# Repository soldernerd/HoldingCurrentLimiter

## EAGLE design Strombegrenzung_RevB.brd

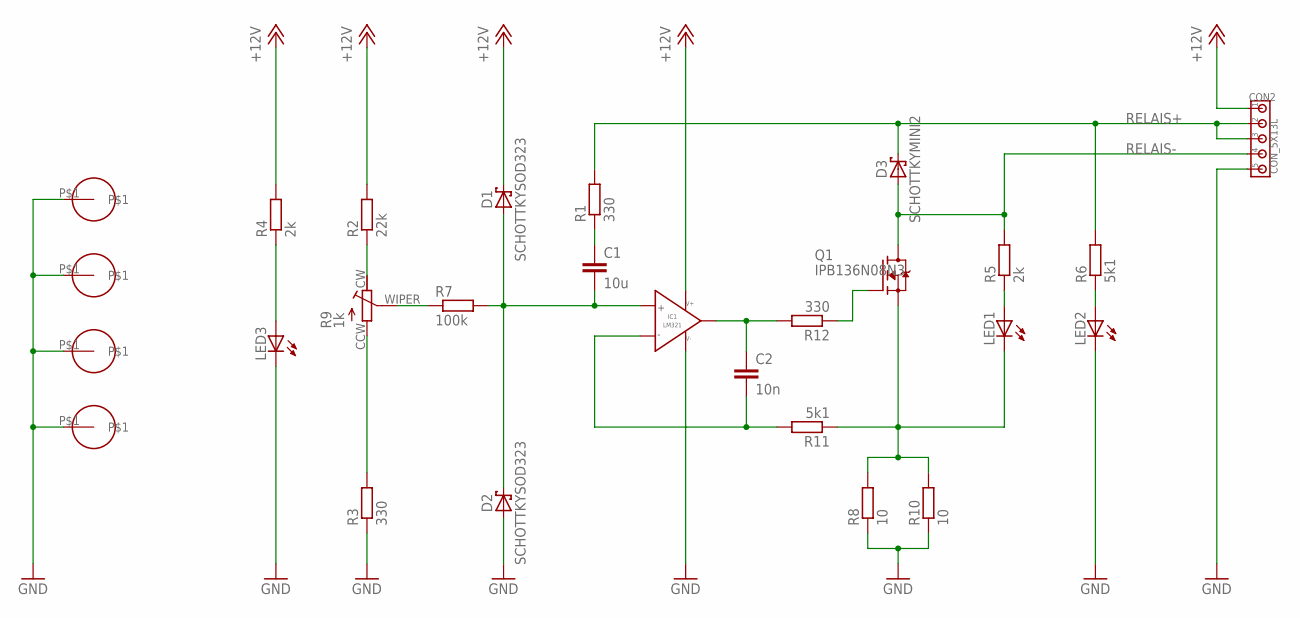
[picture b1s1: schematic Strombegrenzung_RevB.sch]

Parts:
C1: 10u; C1206
C2: 10n; C0805
CON2: CON_5X13L; 200MIL_5X
D1, D2: SCHOTTKYSOD323; SOD323
D3: SCHOTTKYMINI2; MINI2-F3-B
IC1: LM321; SOT-23-5
LED1, LED2, LED3: LED0805
Q1: IPB136N08N3; TO263-3
R1, R3, R12: 330; R0805
R2: 22k; R0805
R4, R5: 2k; R0805
R6, R11: 5k1; R0805
R7: 100k; R0805
R8, R10: 10; R0805
R9: 1k; RTRIM3314G
U$1, U$2, U$3, U$4: HOLE_3.3MM

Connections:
+12V: CON2.1, D1.C, IC1.5 (V+), R2.2, R4.2
GND: CON2.5, D2.A, IC1.2 (V-), LED2.C, LED3.C, R3.1, R8.1, R10.1, U$1.P$1, U$2.P$1, U$3.P$1, U$4.P$1
unnamed: C1.1, R1.1
unnamed: R7.1, R9.WIPER
unnamed: C1.2, D1.A, D2.C, IC1.1 (IN+), R7.2
unnamed: Q1.1 (G), R12.1
unnamed: LED1.A, R5.1
unnamed: LED3.A, R4.1
unnamed: C2.2, IC1.3 (IN-), R11.2
unnamed: R2.1, R9.CW
unnamed: R3.2, R9.CCW
unnamed: C2.1, IC1.4 (VOUT), R12.2
unnamed: LED1.C, Q1.3 (S), R8.2, R10.2, R11.1
R6: LED2.A, R6.1
RELAIS+: CON2.2, CON2.3, D3.C, R1.2, R6.2
RELAIS-: CON2.4, D3.A, Q1.TAB (D), R5.2

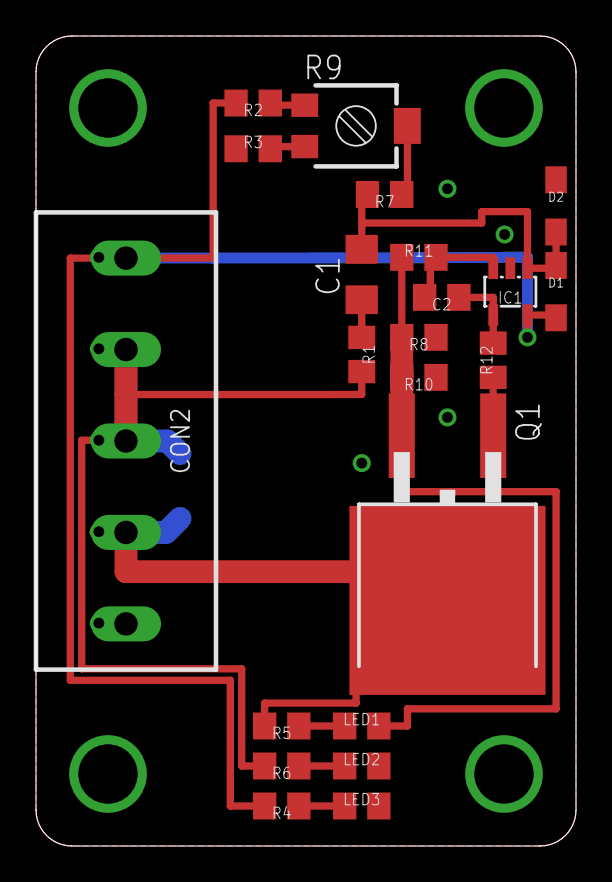
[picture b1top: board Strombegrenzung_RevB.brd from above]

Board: 2 copper layers, 30.0 x 45.0 mm, 27 parts (1 on the bottom side), 16 nets.

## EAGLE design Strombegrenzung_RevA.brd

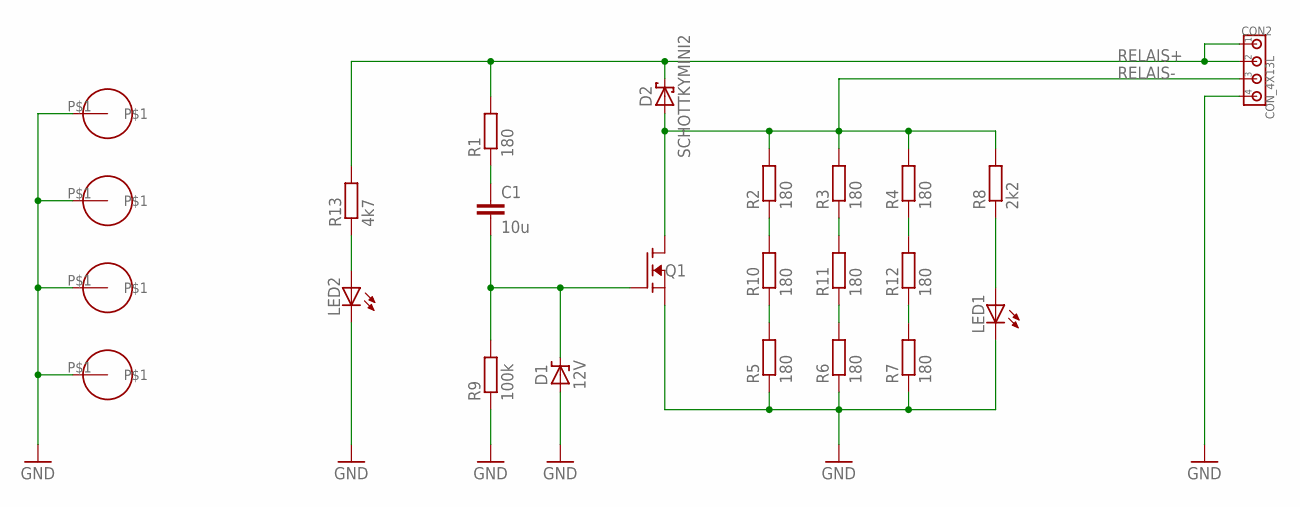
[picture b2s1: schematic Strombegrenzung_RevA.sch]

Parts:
C1: 10u; C1206
CON2: CON_4X13L; 200MIL_4X
D1: 12V; SOD323
D2: SCHOTTKYMINI2; MINI2-F3-B
LED1, LED2: LED0805
Q1: N-FETSOT23; SOT23
R1, R2, R3, R4, R5, R6, R7, R10, R11, R12: 180; R0805
R8: 2k2; R0805
R9: 100k; R0805
R13: 4k7; R0805
U$1, U$2, U$3, U$4: HOLE_3.3MM

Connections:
GND: CON2.4, D1.A, LED1.C, LED2.C, Q1.2 (S), R5.1, R6.1, R7.1, R9.1, U$1.P$1, U$2.P$1, U$3.P$1, U$4.P$1
unnamed: C1.1, R1.1
unnamed: R2.1, R10.2
unnamed: C1.2, D1.C, Q1.1 (G), R9.2
unnamed: R5.2, R10.1
unnamed: LED1.A, R8.1
unnamed: R6.2, R11.1
unnamed: LED2.A, R13.1
unnamed: R3.1, R11.2
unnamed: R4.1, R12.2
unnamed: R7.2, R12.1
RELAIS+: CON2.1, CON2.2, D2.C, R1.2, R13.2
RELAIS-: CON2.3, D2.A, Q1.3 (D), R2.2, R3.2, R4.2, R8.2

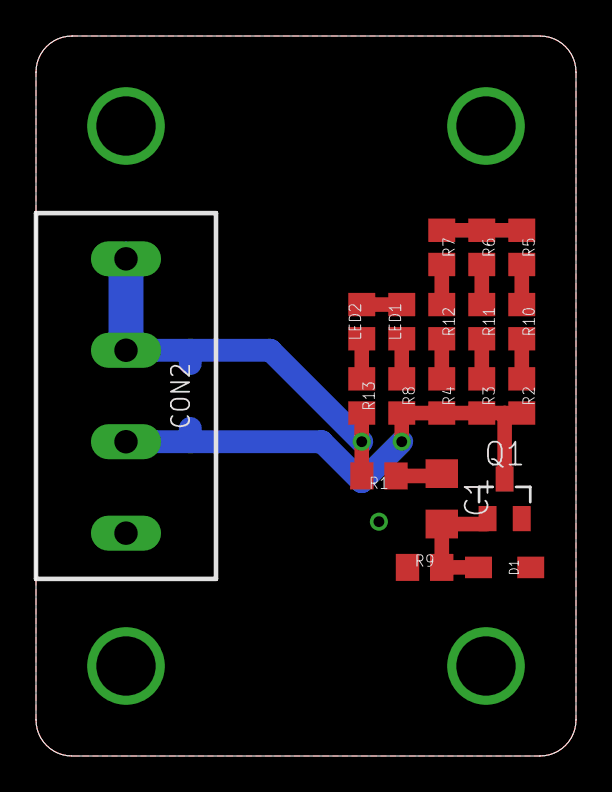
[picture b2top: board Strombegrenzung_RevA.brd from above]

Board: 2 copper layers, 30.0 x 40.0 mm, 24 parts (1 on the bottom side), 13 nets.

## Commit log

2018-08-12 Initial commit but Rev C already finished
